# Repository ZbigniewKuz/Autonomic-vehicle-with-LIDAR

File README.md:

# Autonomic-vehicle-with-LIDAR
This project contain programs, which will be used to control vehicle using mobile phone application to move (MIT app inventor) and connection it to ESP-32 via Bluetooth. 
Next ESP-32 will use UART interface to communicate with STM32 to control engines. Besides the LIDAR scanner on top of the vehicle is going to scann surrounding enviroment and make a map.

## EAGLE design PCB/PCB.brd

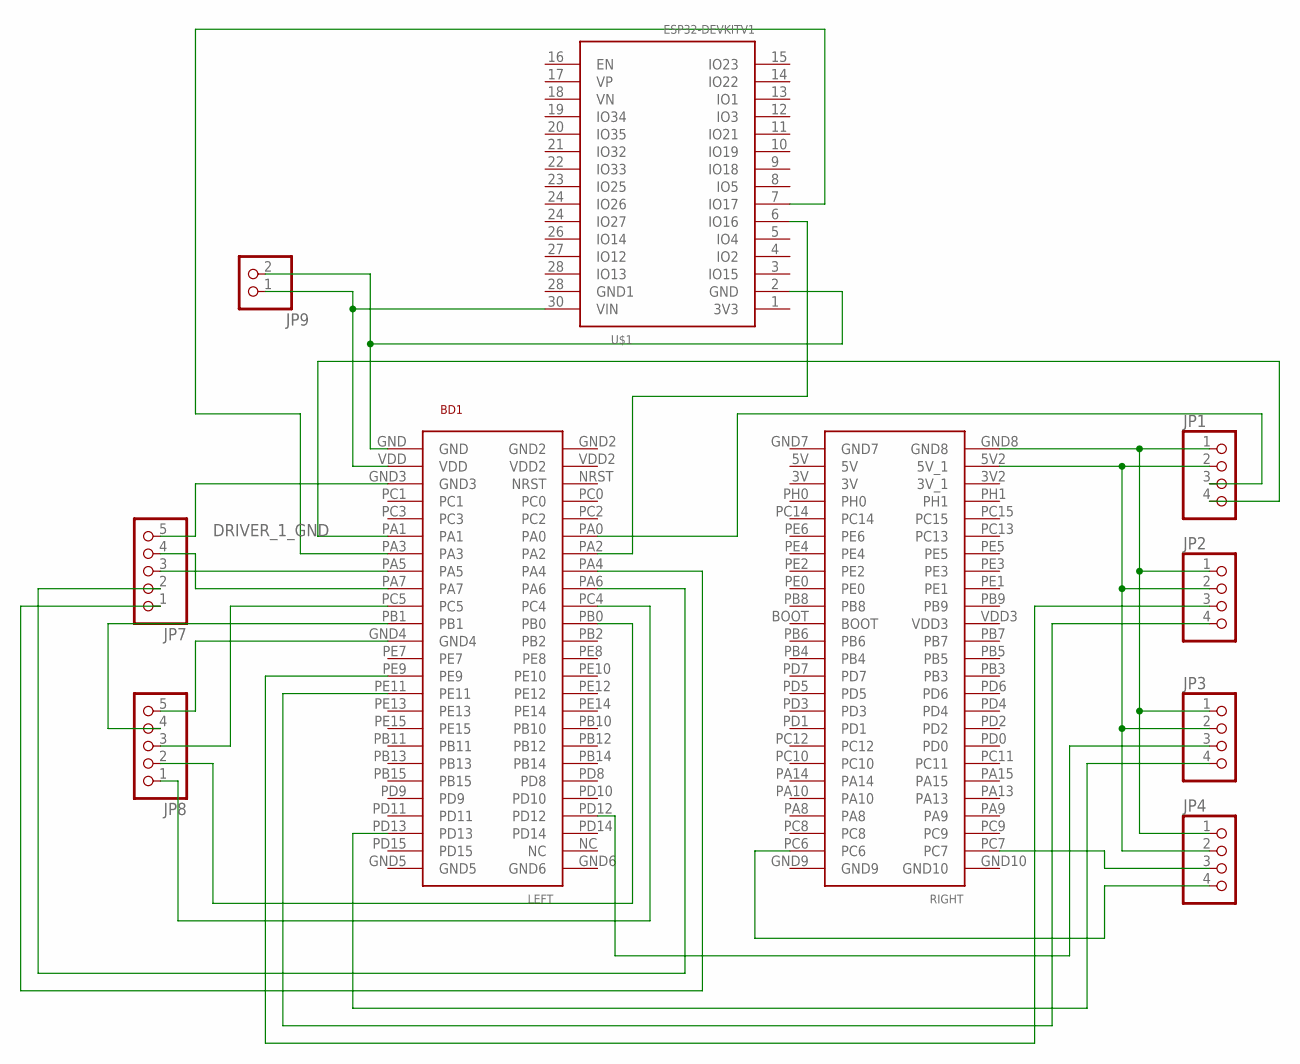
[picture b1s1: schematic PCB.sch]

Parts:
BD1: STM32F4-DISCOVERY; STM32F407VG
JP1, JP2, JP3, JP4: PINHD-1X4; 1X04
JP7, JP8: PINHD-1X5; 1X05
JP9: PINHD-1X2; 1X02
U$1: ESP32DEVKITV1; ESP32-DEVKITV1

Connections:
DRIVER_1_GND: BD1.GND3, JP7.5
unnamed: BD1.VDD, JP9.1, U$1.30 (VIN)
unnamed: BD1.GND, JP9.2, U$1.2 (GND)
unnamed: BD1.GND4, JP8.5
unnamed: BD1.PA7, JP7.4
unnamed: BD1.PA5, JP7.3
unnamed: BD1.PA6, JP7.2
unnamed: BD1.PA4, JP7.1
unnamed: BD1.PB1, JP8.4
unnamed: BD1.PC5, JP8.3
unnamed: BD1.PB0, JP8.2
unnamed: BD1.PC4, JP8.1
unnamed: BD1.PA2, U$1.6 (IO16)
unnamed: BD1.PA3, U$1.7 (IO17)
unnamed: BD1.GND8, JP1.1, JP2.1, JP3.1, JP4.1
unnamed: BD1.5V2 (5V_1), JP1.2, JP2.2, JP3.2, JP4.2
unnamed: BD1.PA1, JP1.4
unnamed: BD1.PA0, JP1.3
unnamed: BD1.PE9, JP2.3
unnamed: BD1.PE11, JP2.4
unnamed: BD1.PD12, JP3.3
unnamed: BD1.PD13, JP3.4
unnamed: BD1.PC7, JP4.3
unnamed: BD1.PC6, JP4.4

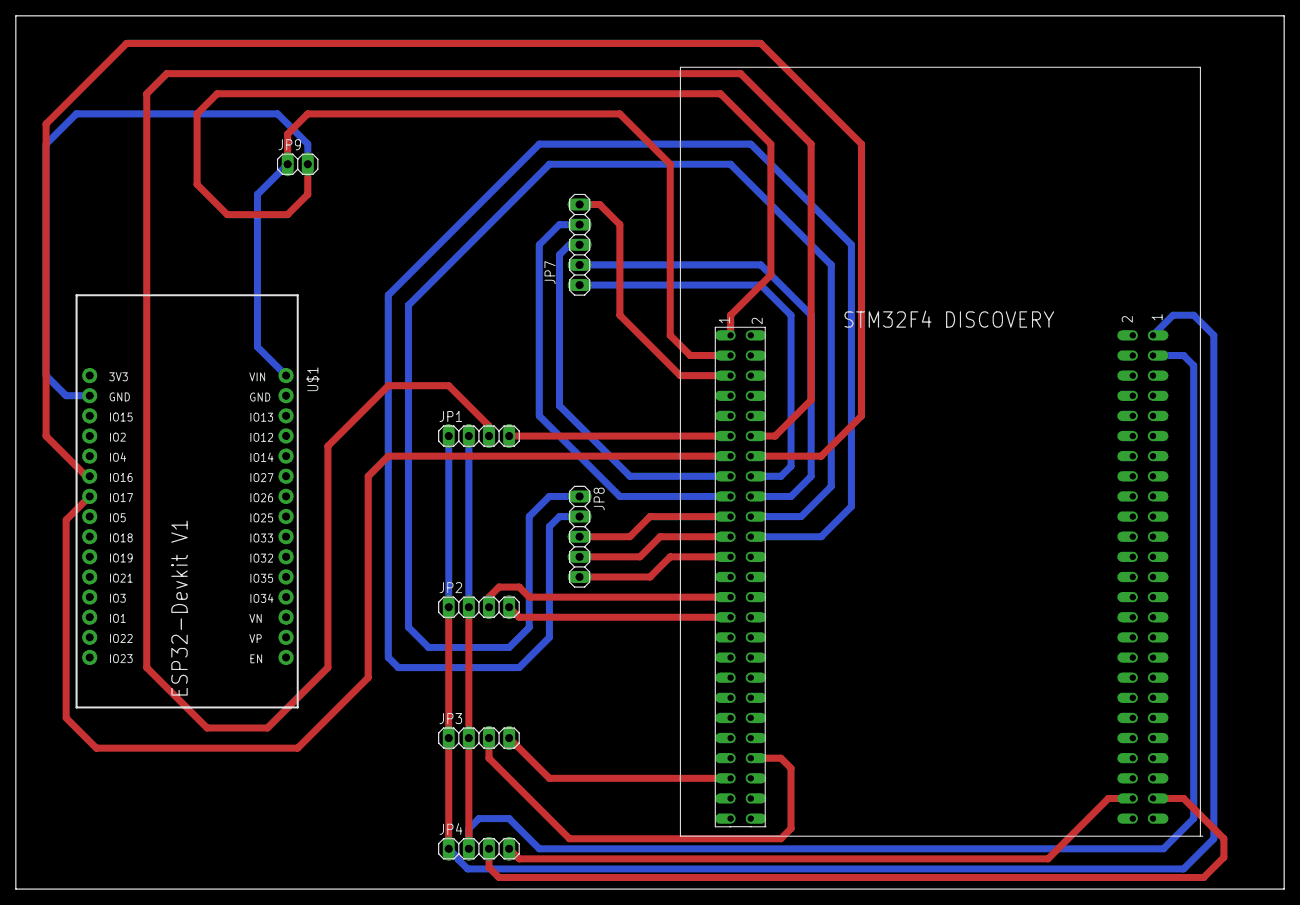
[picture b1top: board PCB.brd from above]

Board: 2 copper layers, 160.0 x 110.2 mm, 9 parts (0 on the bottom side), 24 nets.
